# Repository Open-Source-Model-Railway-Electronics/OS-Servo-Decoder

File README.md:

# OS-Servo-Decoder

The OS-Servo-Decoder is a simple and robust DCC accessory decoder designed for driving up to 8 servo motors. It supports modern model railroads with flexible configuration options, external relay modules for polarity switching (optional) and direct control using both input switches, DCC accessory commands and locomotive functions (F1–F8).

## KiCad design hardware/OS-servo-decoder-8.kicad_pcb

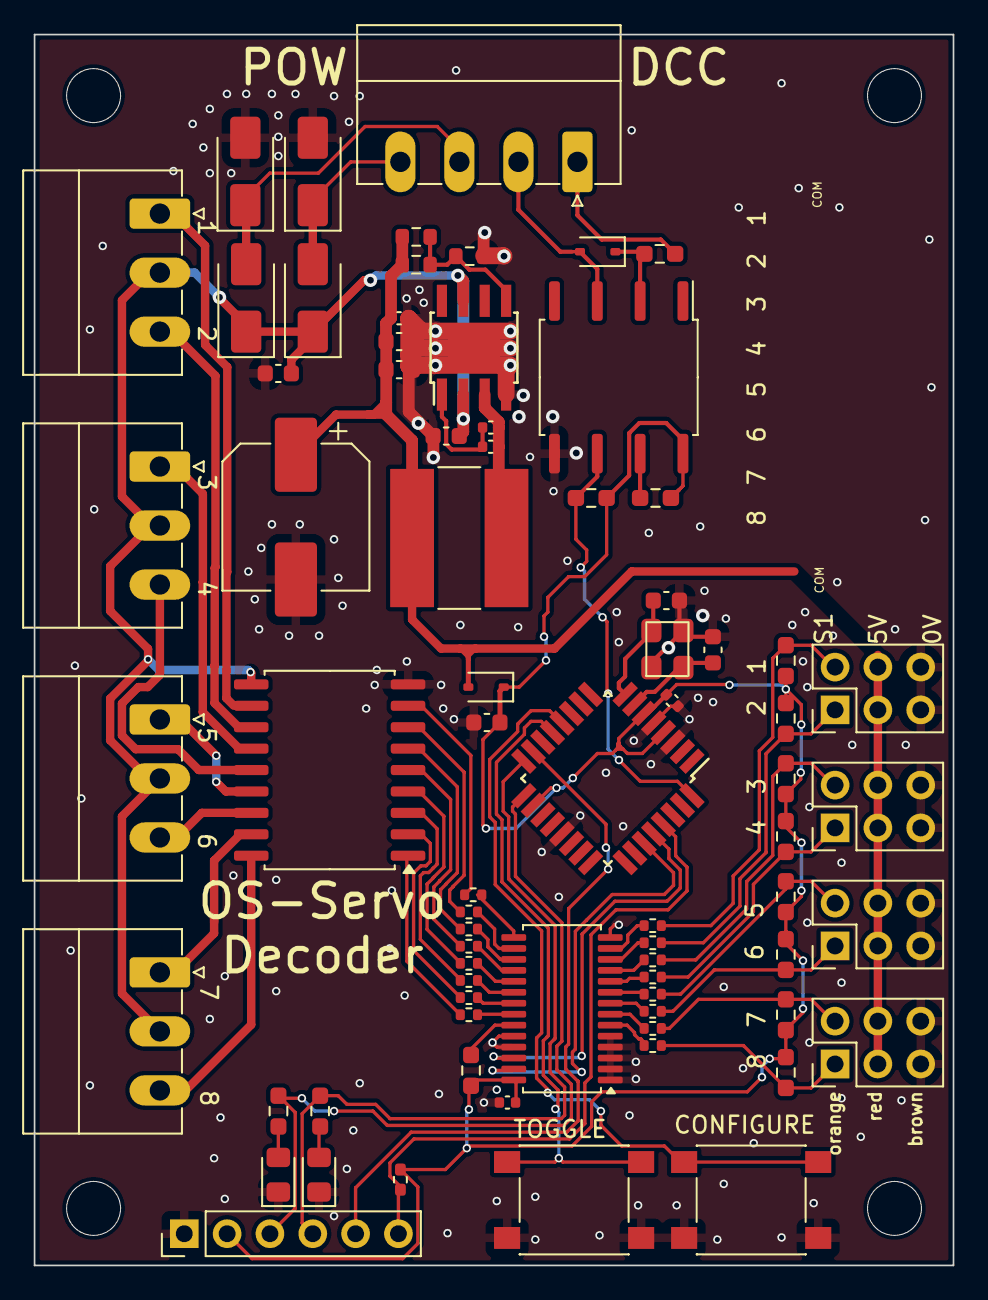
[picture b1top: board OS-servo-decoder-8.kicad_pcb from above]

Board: 2 copper layers, 54.5 x 73.0 mm, 74 parts (0 on the bottom side), 67 nets.

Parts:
C201, C203: 12pF; C_0603_1608Metric
C202, C902, C906, C1601: 100nF; C_0402_1005Metric
C401: 1000uF; CP_Elec_8x10.5
C402, C901, C904, C905: 22uF; C_0603_1608Metric
C501: 100nF; C_0603_1608Metric
C903: 22nF; C_0402_1005Metric
D201, D202: LED; LED_0805_2012Metric_Pad1.15x1.40mm_HandSolder
D401, D1001: 1N4148WS; D_SOD-323
D501, D502, D503, D504: SS53; D_SMA
J101: FEMALE; PhoenixContact_MC_1,5_4-G-3.5_1x04_P3.50mm_Horizontal
J201: ICSP; PinHeader_1x06_P2.54mm_Vertical
J401, J1301, J1401, J1501: Screw_Terminal_01x03; PhoenixContact_MC_1,5_3-G-3.5_1x03_P3.50mm_Horizontal
J701, J801, J901, J1001: Conn_02x03_Odd_Even; PinHeader_2x03_P2.54mm_Vertical
L901: L; L_Bourns-SRN8040_8x8.15mm
R201, R203: 6k2; R_0603_1608Metric_Pad0.98x0.95mm_HandSolder
R202: 10k; R_0402_1005Metric_Pad0.72x0.64mm_HandSolder
R701, R702, R801, R802, R904, R905, R1002, R1003, R1004, R1005, R1601: 10k; R_0603_smalltext
R901: 220k; R_0603_1608Metric
R902: 20k; R_0603_1608Metric
R903: 150k; R_0603_1608Metric
R1001: 1k; R_0603_smalltext
R1602, R1603, R1604, R1605, R1606, R1607, R1608, R1609, R1610, R1611, R1612, R1613, R1614, R1615, R1616, R1617: 220R; R_0402_1005Metric
SW601, SW602: SW_Push; tactile_SMD_6mm
U202: ATmega328-A; TQFP-32_7x7mm_P0.8mm
U901: MT2499A; TI_SO-PowerPAD-8
U1001: 6N137; SOP-8_6.62x9.15mm_P2.54mm
U1101: ULN2803A; SOIC-18W_7.5x11.6mm_P1.27mm
U1601: PCA9685PW; TSSOP-28_4.4x9.7mm_P0.65mm
Y201: Crystal_GND2; crystal_arduino

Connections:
+5V: C202.1, C402.1, C1601.1, D401.1 (K), J201.2, R202.2, R701.2, R702.2, R801.2, R802.2, R904.2, R905.2, R1002.1, R1003.1, R1004.2, R1005.2, R1601.1, U202.4 (VCC), U202.6 (VCC), U202.18 (AVCC), U1001.8 (VCC), U1601.28 (VDD)
+5VA: C401.1, C904.1, C905.1, C906.1, D401.2 (A), J701.3, J701.4, J801.3, J801.4, J901.3, J901.4, J1001.3, J1001.4, L901.2, R901.1, R903.2
/Buck/A: D503.2 (A), D504.1 (K), J101.3
/Buck/B: D501.2 (A), D502.1 (K), J101.4
/Connector/A: D1001.2 (A), J101.2, U1001.3 (C)
/Connector/B: J101.1, R1001.1
/DCC/DCC_TTL: R1003.2, U202.32 (PD2), U1001.6 (VO)
/PCA9685/SCL: U202.28 (PC5), U1601.26 (SCL)
/PCA9685/SDA: U202.27 (PC4), U1601.27 (SDA)
/PCA9685/bus1.pin1: J701.1, R701.1, R1608.2
/PCA9685/bus1.pin2: J701.2, R702.1, R1609.2
/PCA9685/bus2.pin1: J801.1, R801.1, R1606.2
/PCA9685/bus2.pin2: J801.2, R802.1, R1607.2
/PCA9685/bus3.pin1: J901.1, R904.1, R1604.2
/PCA9685/bus3.pin2: J901.2, R905.1, R1605.2
/PCA9685/bus4.pin1: J1001.1, R1004.1, R1602.2
/PCA9685/bus4.pin2: J1001.2, R1005.1, R1603.2
/PCA9685/uln1: R1617.2, U1101.1 (I1)
/PCA9685/uln2: R1616.2, U1101.2 (I2)
/PCA9685/uln3: R1615.2, U1101.3 (I3)
/PCA9685/uln4: R1614.2, U1101.4 (I4)
/PCA9685/uln5: R1613.2, U1101.5 (I5)
/PCA9685/uln6: R1612.2, U1101.6 (I6)
/PCA9685/uln7: R1611.2, U1101.7 (I7)
/PCA9685/uln8: R1610.2, U1101.8 (I8)
/ULN2803/1.pin1: J1301.3, U1101.12 (O7)
/ULN2803/1.pin2: J1301.1, U1101.11 (O8)
/ULN2803/2.pin1: J401.3, U1101.14 (O5)
/ULN2803/2.pin2: J401.1, U1101.13 (O6)
/ULN2803/3.pin1: J1401.3, U1101.16 (O3)
/ULN2803/3.pin2: J1401.1, U1101.15 (O4)
/ULN2803/4.pin1: J1501.3, U1101.18 (O1)
/ULN2803/4.pin2: J1501.1, U1101.17 (O2)
/atmega/LED: J201.3, R201.1, U202.17 (PB5)
/atmega/LED2: J201.4, R203.1, U202.16 (PB4)
/atmega/MOSI: J201.5, U202.15 (PB3)
/atmega/X1: C201.2, U202.7 (XTAL1/PB6), Y201.1
/atmega/X2: C203.2, U202.8 (XTAL2/PB7), Y201.3
/atmega/conf: SW602.2, U202.12 (PB0)
/atmega/reset: J201.6, R202.1, U202.29 (~RESET/PC6)
/atmega/toggle: SW601.2, U202.13 (PB1)
GND: C201.1, C202.2, C203.1, C401.2, C402.2, C501.2, C901.2, C904.2, C905.2, C906.2, C1601.2, D201.1 (K), D202.1 (K), D502.2 (A), D504.2 (A), J201.1, J701.5, J701.6, J801.5, J801.6, J901.5, J901.6, J1001.5, J1001.6, R902.2, SW601.1, SW602.1, U202.3 (GND), U202.5 (GND), U202.21 (GND), U901.4 (GND), U901.9 (GND), U1001.5 (GND), U1101.9 (GND), U1601.1 (A0), U1601.2 (A1), U1601.3 (A2), U1601.4 (A3), U1601.5 (A4), U1601.14 (VSS), U1601.24 (A5), U1601.25 (EXTCLK), Y201.2 (GND), Y201.4 (GND)
unnamed: D201.2 (A), R201.2
unnamed: D202.2 (A), R203.2
unnamed: D1001.1 (K), R1001.2, U1001.2 (A)
unnamed: C902.1, C903.1, U901.1 (BS)
unnamed: R901.2, R902.1, R903.1, U901.5 (FB)
unnamed: C902.2, C903.2, L901.1, U901.3 (SW)
unnamed: R1002.2, U1001.7 (EN)
unnamed: R1602.1, U1601.6 (LED0)
unnamed: R1603.1, U1601.7 (LED1)
unnamed: R1604.1, U1601.8 (LED2)
unnamed: R1605.1, U1601.9 (LED3)
unnamed: R1606.1, U1601.10 (LED4)
unnamed: R1607.1, U1601.11 (LED5)
unnamed: R1608.1, U1601.12 (LED6)
unnamed: R1609.1, U1601.13 (LED7)
unnamed: R1610.1, U1601.15 (LED8)
unnamed: R1611.1, U1601.16 (LED9)
unnamed: R1612.1, U1601.17 (LED10)
unnamed: R1613.1, U1601.18 (LED11)
unnamed: R1614.1, U1601.19 (LED12)
unnamed: R1615.1, U1601.20 (LED13)
unnamed: R1616.1, U1601.21 (LED14)
unnamed: R1617.1, U1601.22 (LED15)
unnamed: R1601.2, U1601.23 (~OE)
VCC: C501.1, C901.1, D501.1 (K), D503.1 (K), J401.2, J1301.2, J1401.2, J1501.2, U901.2 (Vin), U901.7 (EN), U1101.10 (COM)

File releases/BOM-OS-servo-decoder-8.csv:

Comment,Designator,Footprint,LCSC
6N137,U1001,SOP-8_6.62x9.15mm_P2.54mm,C110020
Crystal_GND2,Y201,crystal_arduino,C13738
100nF,C501,C_0603_1608Metric,C14663
ATmega328-A,U202,TQFP-32_7x7mm_P0.8mm,C14877
22nF,C903,C_0402_1005Metric,C1532
ULN2803A,U1101,SOIC-18W_7.5x11.6mm_P1.27mm,C181731
1k,R1001,R_0603_smalltext,C21190
1N4148WS,"D1001,D401",D_SOD-323,C2128
150k,R903,R_0603_1608Metric,C22807
220k,R901,R_0603_1608Metric,C22961
220R,"R1602,R1603,R1604,R1605,R1606,R1607,R1608,R1609,R1610,R1611,R1612,R1613,R1614,R1615,R1616,R1617",R_0402_1005Metric,C25091
10k,R202,R_0402_1005Metric_Pad0.72x0.64mm_HandSolder,C25744
10k,"R1002,R1003,R1004,R1005,R1601,R701,R702,R801,R802,R904,R905",R_0603_smalltext,C25804
PCA9685PW,U1601,TSSOP-28_4.4x9.7mm_P0.65mm,C2678753
L,L901,L_Bourns-SRN8040_8x8.15mm,C2929438
SW_Push,"SW601,SW602",tactile_SMD_6mm,C294567
MT2499A,U901,TI_SO-PowerPAD-8,C3007555
100nF,"C1601,C202,C902,C906",C_0402_1005Metric,C307331
12pF,"C201,C203",C_0603_1608Metric,C38523
6k2,"R201,R203",R_0603_1608Metric_Pad0.98x0.95mm_HandSolder,C4260
20k,R902,R_0603_1608Metric,C4328
22uF,"C402,C901,C904,C905",C_0603_1608Metric,C45783
1000uF,C401,CP_Elec_8x10.5,C5162347
Conn_02x03_Odd_Even,"J1001,J701,J801,J901",PinHeader_2x03_P2.54mm_Vertical,C65114
LED,"D201,D202",LED_0805_2012Metric_Pad1.15x1.40mm_HandSolder,C84256
SS53,"D501,D502,D503,D504",D_SMA,C8678
Screw_Terminal_01x03,"J1301,J1401,J1501,J401","PhoenixContact_MC_1,5_3-G-3.5_1x03_P3.50mm_Horizontal",C880573
FEMALE,J101,"PhoenixContact_MC_1,5_4-G-3.5_1x04_P3.50mm_Horizontal",C880574
Screw_Terminal_01x10,J501,"TerminalBlock_Phoenix_MPT-0,5-10-2.54_1x10_P2.54mm_Horizontal",

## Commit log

2025-06-13 added initial files
2025-06-17 added or renamed PNG preview
2025-06-18 deleted source code in favor of sub module
2025-06-18 Temporarily removed submodule to refactor layout
2025-06-18 Add submodule OS-Servo-Decoder-Core in software/
2025-06-19 Toegevoegd: handleiding (manual.odt)
2025-06-19 Hersteld: handleiding toegevoegd in docs/
2025-06-26 update board file, made similar to OS solenoid decoder
2025-07-22 added manual and picture
2025-10-27 removed obsolete build and upload files
2025-11-07 changed manual to markdown style
2025-11-15 upadted readme
2026-05-24 added translations
